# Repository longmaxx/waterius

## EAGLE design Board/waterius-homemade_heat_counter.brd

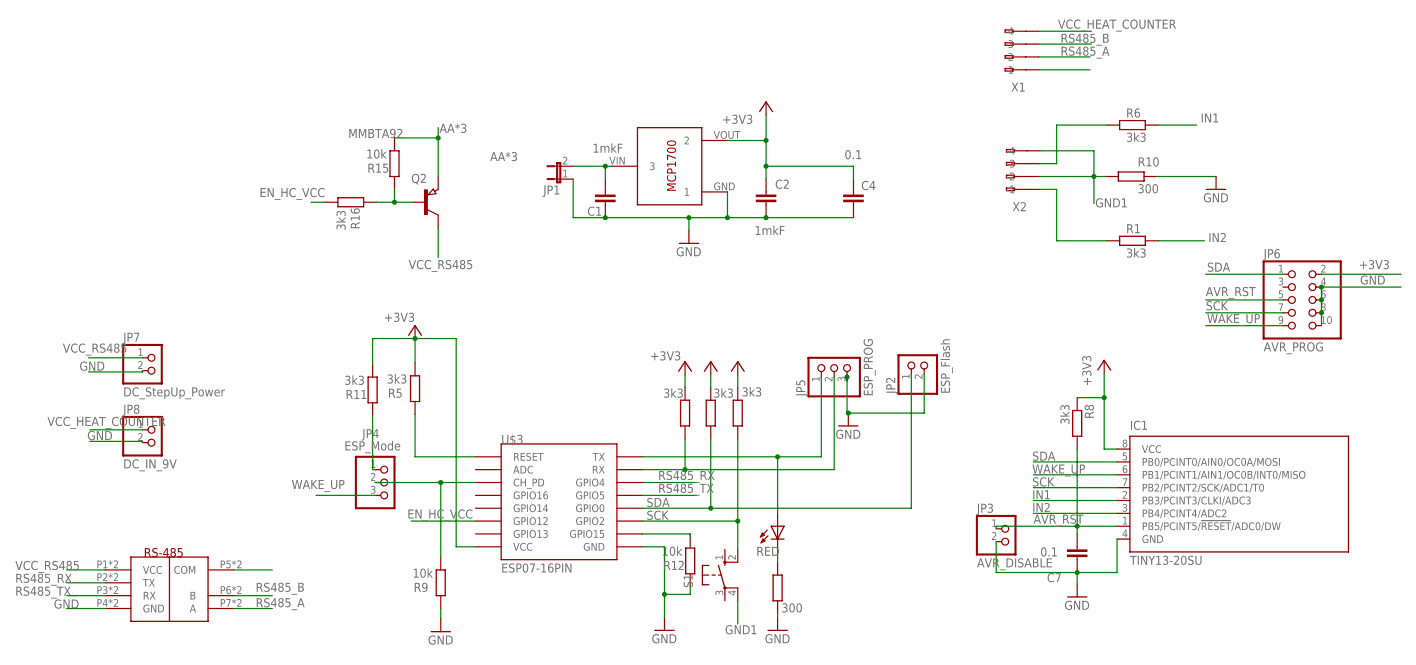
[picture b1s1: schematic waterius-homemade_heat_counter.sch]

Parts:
C1, C2: 1mkF; C0805
C4, C7: 0.1; C0805
IC1: TINY13-20SU; 8S2
JP1: JP1E; JP1
JP2: ESP_Flash; 1X02
JP3: AVR_DISABLE; 1X02
JP4: ESP_Mode; 1X03
JP5: ESP_PROG; 1X03
JP6: AVR_PROG; 2X05
JP7: DC_StepUp_Power; 1X02
JP8: DC_IN_9V; 1X02
LED1: RED; CHIPLED_0805
Q2: MMBTA92; SOT23
R1, R6: 3k3; M0805
R2, R3, R5, R7, R8, R11, R16: 3k3; R0805
R4: 300; R0805
R9, R12, R15: 10k; R0805
R10: 300; M0805
S1: 10-XX; B3F-10XX
U1: RS-485-MODULE; DIP_MODULE
U$2: MCP1700T-3302E/TT
U$3: ESP07-16PIN
X1, X2: 233-104

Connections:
+3V3: C2.1, C4.1, IC1.8 (VCC), JP6.2, R2.1, R3.1, R5.1, R7.1, R8.1, R11.1, U$2.VOUT (2), U$3.VCC
AA*3: C1.1, JP1.2, Q2.2 (E), R15.1, U$2.VIN (3)
AVR_RST: C7.2, IC1.1 (PB5/PCINT5/!RESET!/ADC0/DW), JP3.1, JP6.5, R8.2
EN_HC_VCC: R16.1, U$3.GPIO12
GND: C1.2, C2.2, C4.2, C7.1, IC1.4 (GND), JP1.1, JP2.2, JP3.2, JP5.3, JP6.4, JP6.6, JP6.8, JP6.10, JP7.2, JP8.2, R4.2, R9.2, R10.2, R12.2, U1.P4 (GND), U1.P13 (GND), U$2.GND (1), U$3.GND
GND1: R10.1, S1.4 (P1), X2.A2 (-2), X2.A4 (-4)
IN1: IC1.2 (PB3/PCINT3/CLKI/ADC3), R6.2
IN2: IC1.3 (PB4/PCINT4/ADC2), R1.2
unnamed: JP5.1, LED1.A, U$3.TX
unnamed: R5.2, U$3.REST (RESET)
unnamed: R6.1, X2.A3 (-3)
unnamed: R1.1, X2.A1 (-1)
unnamed: JP5.2, R7.2, U$3.RX
unnamed: LED1.C, R4.1
unnamed: JP4.2, R9.1, U$3.CH_PD
unnamed: JP4.1, R11.2
unnamed: R12.1, U$3.GPIO15
unnamed: Q2.1 (B), R15.2, R16.2
unnamed: U1.P5 (COM), U1.P14 (COM)
RS485_A: U1.P7 (A), U1.P8 (A), X1.A2 (-2)
RS485_B: U1.P6 (B), U1.P9 (B), X1.A3 (-3)
RS485_RX: U1.P2 (TX), U1.P11 (TX), U$3.GPIO4
RS485_TX: U1.P3 (RX), U1.P12 (RX), U$3.GPIO5
SCK: IC1.7 (PB2/PCINT2/SCK/ADC1/T0), JP6.7, R2.2, S1.2 (S1), U$3.GPIO2
SDA: IC1.5 (PB0/PCINT0/AIN0/OC0A/MOSI), JP2.1, JP6.1, R3.2, U$3.GPIO0
VCC_HEAT_COUNTER: JP8.1, X1.A4 (-4)
VCC_RS485: JP7.1, Q2.3 (C), U1.P1 (VCC), U1.P10 (VCC)
WAKE_UP: IC1.6 (PB1/PCINT1/AIN1/OC0B/INT0/MISO), JP4.3, JP6.9

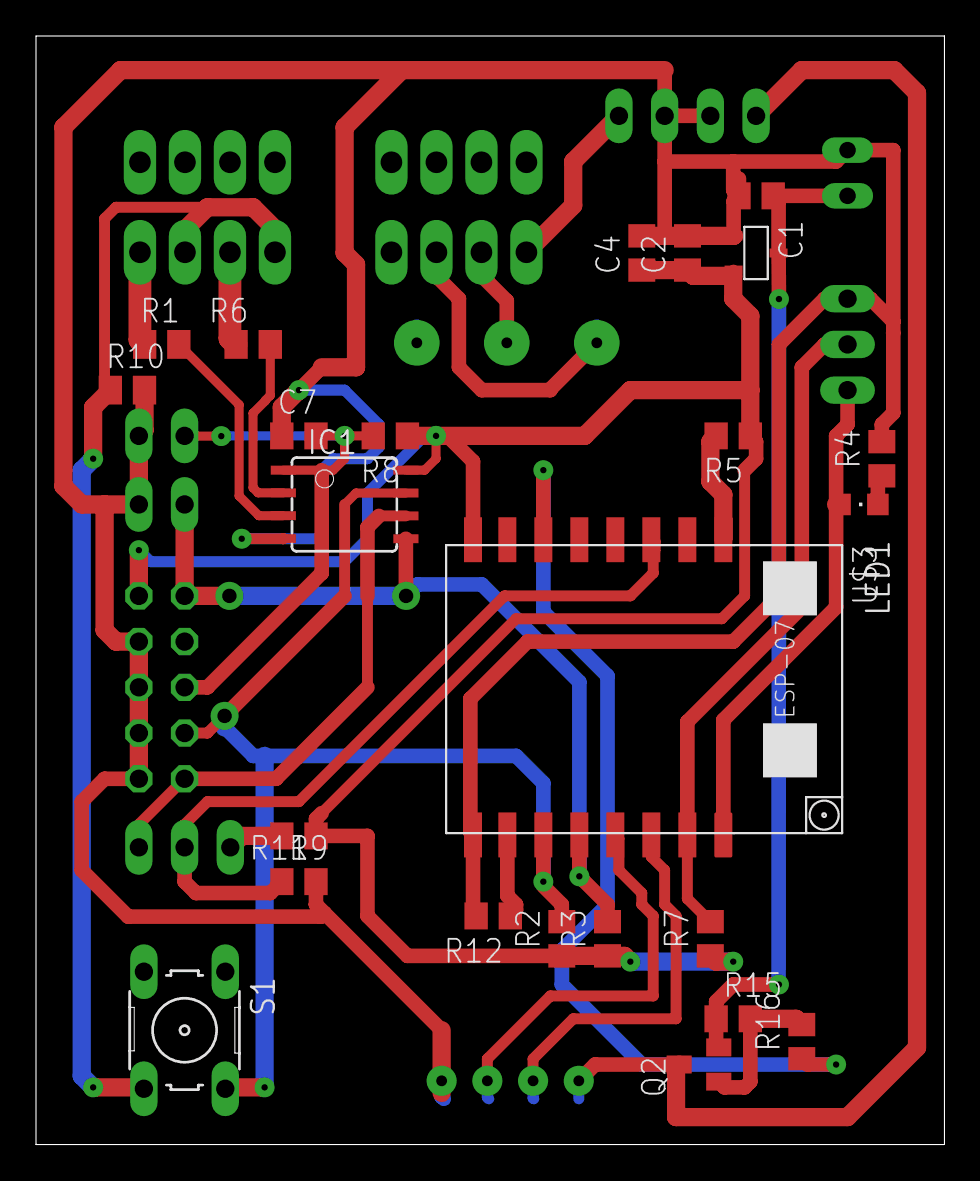
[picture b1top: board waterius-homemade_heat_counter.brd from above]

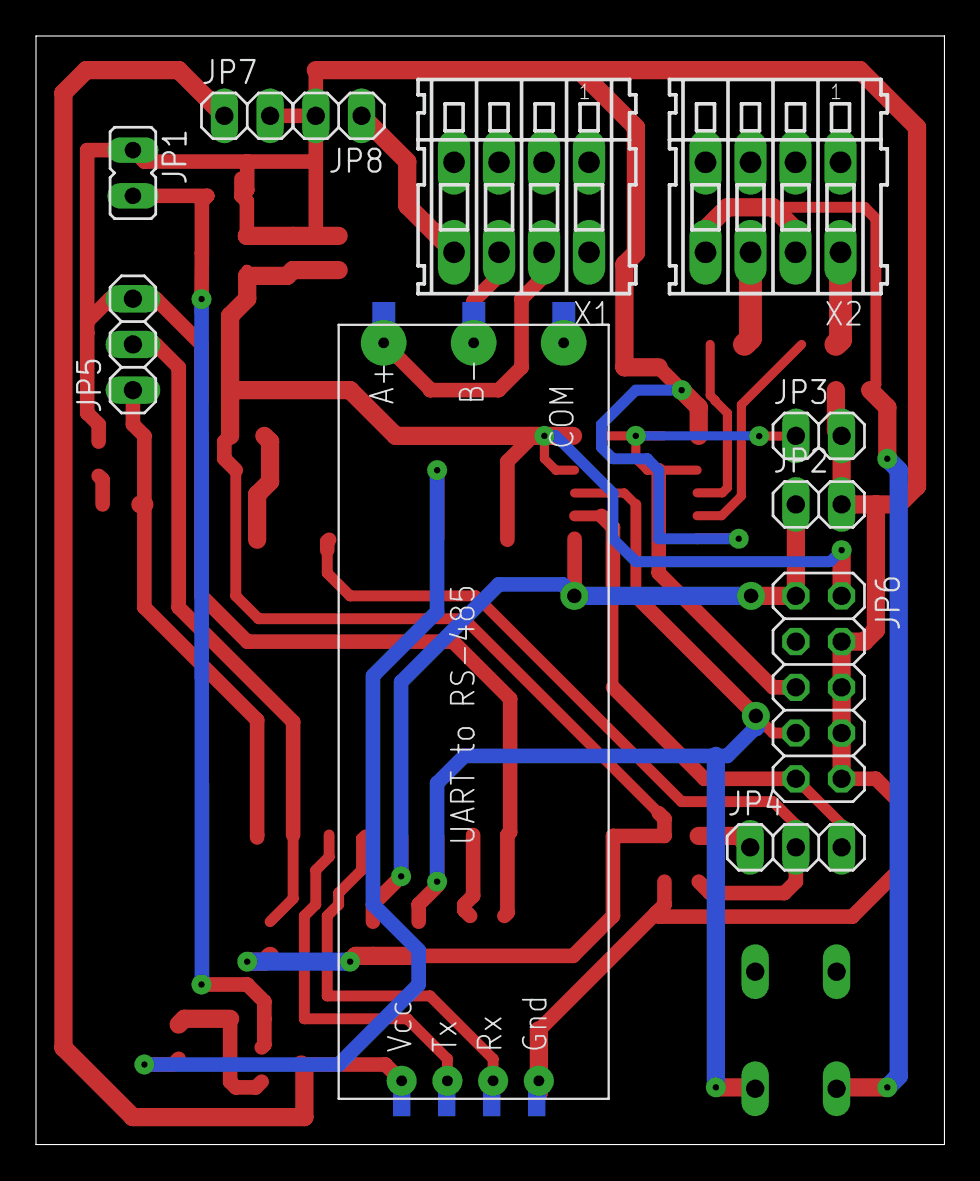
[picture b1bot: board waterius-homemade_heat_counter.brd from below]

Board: 2 copper layers, 50.5 x 61.6 mm, 35 parts (11 on the bottom side), 28 nets.

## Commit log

2020-11-10 compiler Failed to convert Russian symbol for some reason
2020-11-10 remove avr version from config
    1.15 is too old. 3.0.0 is actual
2020-11-26 Fix compilation error. Russian 'I' breaks.
2021-03-21 Heat counter Initial code
2022-11-27 pins esp12
2022-11-27 compilation errors fix
2022-11-28 fix data hc
2022-11-28 send HC mqtt
2022-11-28 hc power pins and power mode
2022-12-07 default dev
2022-12-07 to debug
2022-12-08 wifi
2022-12-11 fix getting hc values
2022-12-11 log messages
2022-12-11 disable send and do sleep 60000
2022-12-11 don't reset mem because of default values
2022-12-11 hc no answer err
2022-12-11 build flags reorganize
2022-12-12 hc no answer err
    (cherry picked from commit d389d7bc89cebf98a1d316e05095f9e8f3081094)
2022-12-30 board with rs-485 interface
2022-12-30 hold heat counter address in settings
2023-01-11 sett Web1
2023-01-19 hc_addr options save
2023-01-19 all to debug
2023-01-19 set and save HC Serial
2023-01-25 debug fixes
2023-02-04 reset hcdata
2023-10-24 after merge upstream master fixes
2023-10-24 disabler my mqtt_hc send
2023-10-27 rewire1
2023-10-27 remove 1 trans
2023-10-30 uncomment mqtt
2023-10-30 esp12 env
2023-11-03 dbg error out
2023-11-03 fix reading data
2023-11-03 Pulsar protocol datasheet
2023-11-11 updates and dbg
2023-11-20 dbg loging
2025-01-20 правка после мержа
2025-01-20 Настройка и сохранение данных счетчика Пульсар в новом коде проекта
2026-01-04 fixes after merge upstream
